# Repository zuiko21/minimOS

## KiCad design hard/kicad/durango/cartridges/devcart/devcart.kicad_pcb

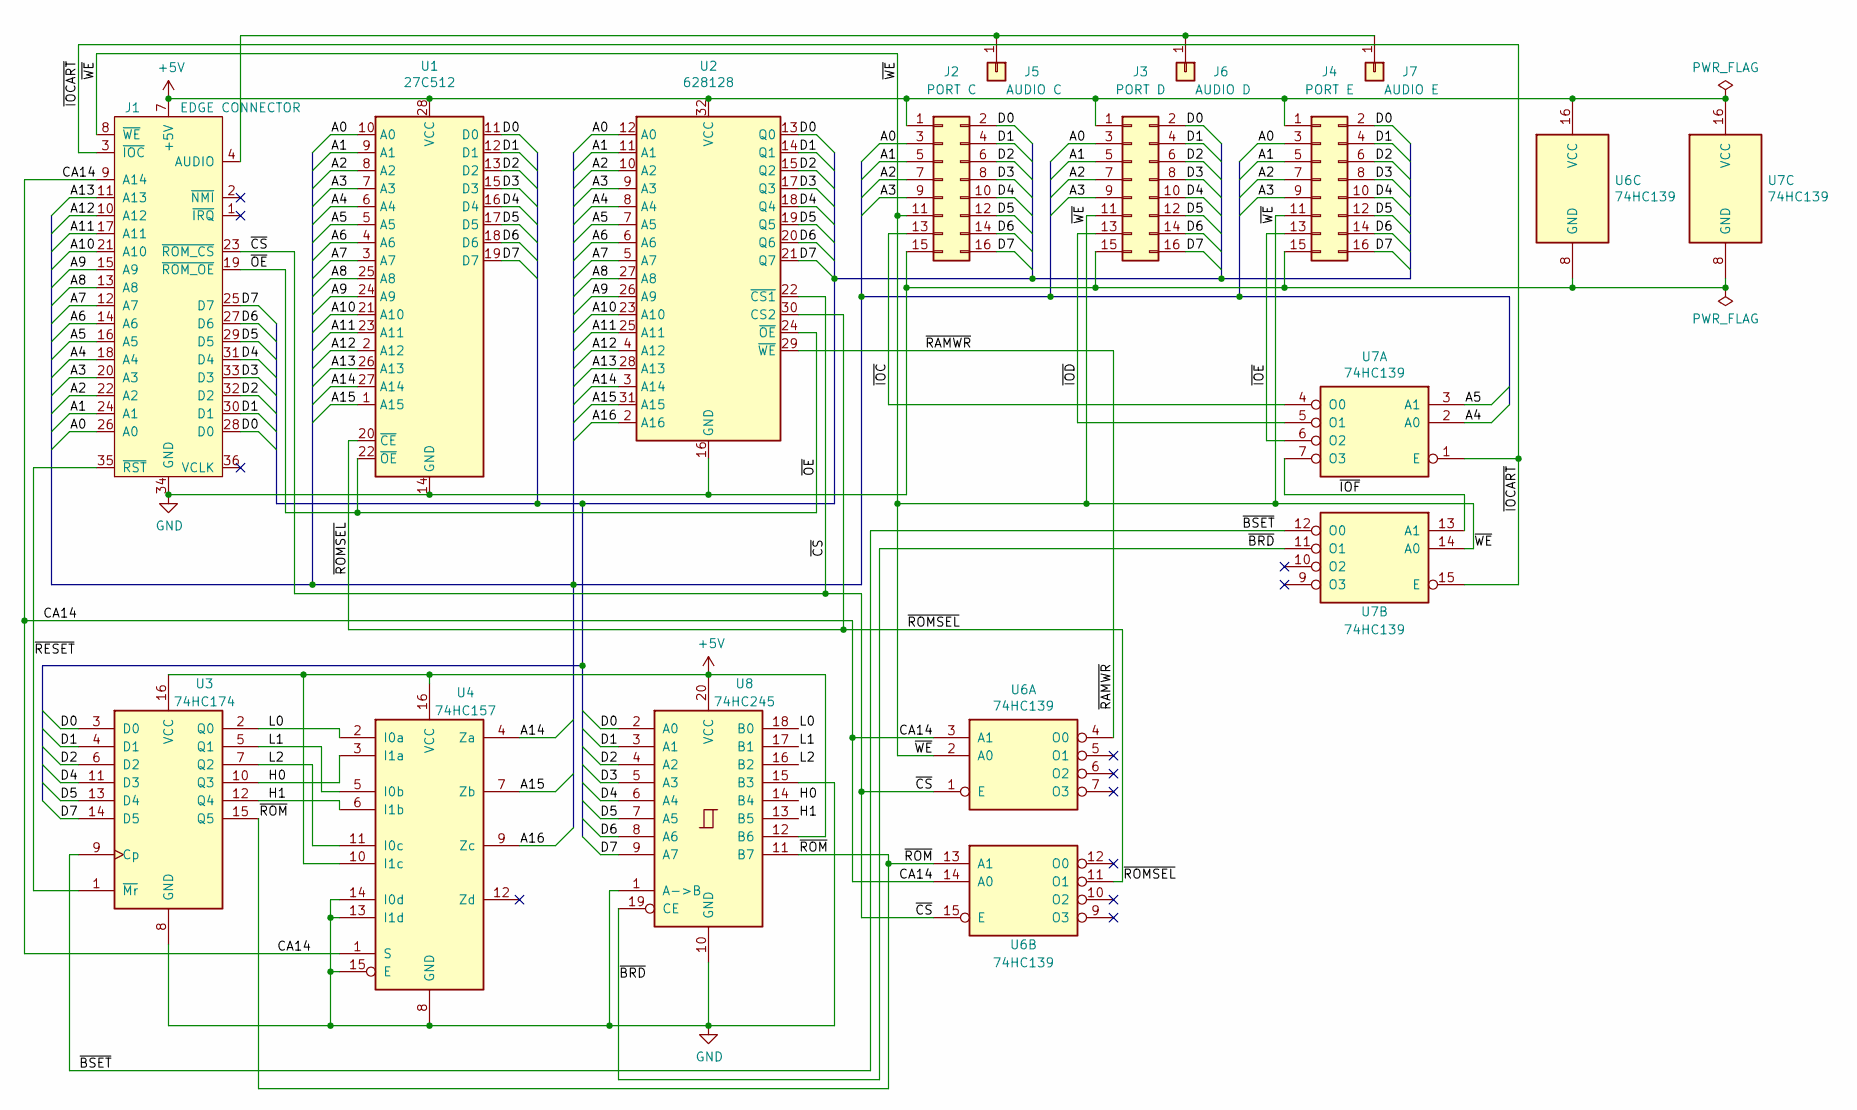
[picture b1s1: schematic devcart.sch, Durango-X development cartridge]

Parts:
J1: EDGE CONNECTOR; Durango_ROM
J2: PORT C; IDC-Header_2x08_P2.54mm_Vertical
J3: PORT D; IDC-Header_2x08_P2.54mm_Vertical
J4: PORT E; IDC-Header_2x08_P2.54mm_Vertical
J5: AUDIO C; PinSocket_1x01_P2.54mm_Vertical
J6: AUDIO D; PinSocket_1x01_P2.54mm_Vertical
J7: AUDIO E; PinSocket_1x01_P2.54mm_Vertical
U1: 27C512; DIP_Socket-28_W11.9_W12.7_W15.24_W17.78_W18.5_3M_228-1277-0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
U2: 628128; DIP-32_W15.24mm
U3: 74HC174; DIP-16_W7.62mm
U4: 74HC157; DIP-16_W7.62mm
U6, U7: 74HC139; DIP-16_W7.62mm
U8: 74HC245; DIP-20_W7.62mm

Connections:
+5V: J1.7 (+5V), J2.1, J3.1, J4.1, U1.28 (VCC), U2.32 (VCC), U3.16 (VCC), U4.10 (I1c), U4.16 (VCC), U6.16 (VCC), U7.16 (VCC), U8.12 (B6), U8.20 (VCC)
/A0: J1.26 (A0), J2.3, J3.3, J4.3, U1.10 (A0), U2.12 (A0)
/A1: J1.24 (A1), J2.5, J3.5, J4.5, U1.9 (A1), U2.11 (A1)
/A2: J1.22 (A2), J2.7, J3.7, J4.7, U1.8 (A2), U2.10 (A2)
/A3: J1.20 (A3), J2.9, J3.9, J4.9, U1.7 (A3), U2.9 (A3)
/A4: J1.18 (A4), U1.6 (A4), U2.8 (A4), U7.2 (A0)
/A5: J1.16 (A5), U1.5 (A5), U2.7 (A5), U7.3 (A1)
/A6: J1.14 (A6), U1.4 (A6), U2.6 (A6)
/A7: J1.12 (A7), U1.3 (A7), U2.5 (A7)
/A8: J1.13 (A8), U1.25 (A8), U2.27 (A8)
/A9: J1.15 (A9), U1.24 (A9), U2.26 (A9)
/A10: J1.21 (A10), U1.21 (A10), U2.23 (A10)
/A11: J1.17 (A11), U1.23 (A11), U2.25 (A11)
/A12: J1.10 (A12), U1.2 (A12), U2.4 (A12)
/A13: J1.11 (A13), U1.26 (A13), U2.28 (A13)
/A14: U1.27 (A14), U2.3 (A14), U4.4 (Za)
/A15: U1.1 (A15), U2.31 (A15), U4.7 (Zb)
/A16: U2.2 (A16), U4.9 (Zc)
/CA14: J1.9 (A14), U4.1 (S), U6.3 (A1), U6.14 (A0)
/D0: J1.28 (D0), J2.2, J3.2, J4.2, U1.11 (D0), U2.13 (Q0), U3.3 (D0), U8.2 (A0)
/D1: J1.30 (D1), J2.4, J3.4, J4.4, U1.12 (D1), U2.14 (Q1), U3.4 (D1), U8.3 (A1)
/D2: J1.32 (D2), J2.6, J3.6, J4.6, U1.13 (D2), U2.15 (Q2), U3.6 (D2), U8.4 (A2)
/D3: J1.33 (D3), J2.8, J3.8, J4.8, U1.15 (D3), U2.17 (Q3), U8.5 (A3)
/D4: J1.31 (D4), J2.10, J3.10, J4.10, U1.16 (D4), U2.18 (Q4), U3.11 (D3), U8.6 (A4)
/D5: J1.29 (D5), J2.12, J3.12, J4.12, U1.17 (D5), U2.19 (Q5), U3.13 (D4), U8.7 (A5)
/D6: J1.27 (D6), J2.14, J3.14, J4.14, U1.18 (D6), U2.20 (Q6), U8.8 (A6)
/D7: J1.25 (D7), J2.16, J3.16, J4.16, U1.19 (D7), U2.21 (Q7), U3.14 (D5), U8.9 (A7)
/H0: U3.10 (Q3), U4.3 (I1a), U8.14 (B4)
/H1: U3.12 (Q4), U4.6 (I1b), U8.13 (B5)
/L0: U3.2 (Q0), U4.2 (I0a), U8.18 (B0)
/L1: U3.5 (Q1), U4.5 (I0b), U8.17 (B1)
/L2: U3.7 (Q2), U4.11 (I0c), U8.16 (B2)
/~BRD: U7.11 (O1), U8.19 (CE)
/~BSET: U3.9 (Cp), U7.12 (O0)
/~CS: J1.23 (~ROM_CS), U2.22 (~CS1), U6.1 (E), U6.15 (E)
/~IOC: J2.13, U7.4 (O0)
/~IOCART: J1.3 (~IOC), U7.1 (E), U7.15 (E)
/~IOD: J3.13, U7.5 (O1)
/~IOE: J4.13, U7.6 (O2)
/~IOF: U7.7 (O3), U7.13 (A1)
/~OE: J1.19 (~ROM_OE), U1.22 (~OE), U2.24 (~OE)
/~RAMWR: U2.29 (~WE), U6.4 (O0)
/~RESET: J1.35 (~RST), U3.1 (~Mr)
/~ROM: U3.15 (Q5), U6.13 (A1), U8.11 (B7)
/~ROMSEL: U1.20 (~CE), U2.30 (CS2), U6.11 (O1)
/~WE: J1.8 (~WE), J2.11, J3.11, J4.11, U6.2 (A0), U7.14 (A0)
GND: J1.34 (GND), J2.15, J3.15, J4.15, U1.14 (GND), U2.16 (GND), U3.8 (GND), U4.8 (GND), U4.13 (I1d), U4.14 (I0d), U4.15 (E), U6.8 (GND), U7.8 (GND), U8.1 (A->B), U8.10 (GND), U8.15 (B3)
unnamed: J1.4 (AUDIO), J5.1, J6.1, J7.1

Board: 2 copper layers, 14 parts (0 on the bottom side), 48 nets, no tracks yet.

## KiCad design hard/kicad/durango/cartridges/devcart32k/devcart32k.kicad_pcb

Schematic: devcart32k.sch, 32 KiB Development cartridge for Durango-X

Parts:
C1: 22n; C_Rect_L7.0mm_W3.5mm_P5.00mm
J1: to Computer; Durango_ROM
J2: SD Interface; PinHeader_2x08_P2.54mm_Vertical
LOGO1: Logo_Open_Hardware_Large; OSHW-Logo2_24.3x20mm_SilkScreen
LOGO2: Logo_Open_Hardware_Small; jaqueria
LOGO3: Logo_Open_Hardware_Small; durango-x90
U1: 27/28C256; DIP_Socket-28_W11.9_W12.7_W15.24_W17.78_W18.5_3M_228-1277-0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
U2: 62256; DIP-28_W15.24mm_Socket
U4: 74HC174; DIP-16_W7.62mm_Socket
U5, U7: 74HC139; DIP-16_W7.62mm_Socket
U6: 74HC245; DIP-20_W7.62mm_Socket

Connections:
+5V: C1.2, J1.7, J2.5, J2.6, U1.1 (VPP), U1.27 (A14), U1.28 (VCC), U2.28 (VCC), U4.14 (D5), U4.16 (VCC), U5.16 (VCC), U6.14 (B4), U6.15 (B3), U6.20 (VCC), U7.14 (A0), U7.16 (VCC)
/G~WE: U2.27 (~WE~), U7.4 (O0)
/MCLK: J2.11, J2.12, U4.2 (Q0), U6.18 (B0)
/MISO: J2.13, J2.14, U6.11 (B7)
/MOSI: J2.9, J2.10, U4.5 (Q1), U6.17 (B1)
/RAM~OE: U2.22 (~OE~), U7.9 (O3)
/ROM~OE: U1.22 (~OE), U7.11 (O1)
/~BL0: U5.3 (A1), U5.12 (O0)
/~CS: J1.23, U1.20 (~CE), U2.20 (~CS), U7.1 (E)
/~IOC: J1.3, U5.1 (E)
/~LATCH: U4.9 (Cp), U5.4 (O0)
/~OE: J1.19, U7.15 (E)
/~ROMEN: U4.12 (Q4), U6.12 (B6), U7.13 (A1)
/~RST: J1.35, U4.1 (~Mr)
/~SSEL: J2.7, J2.8, U4.7 (Q2), U6.16 (B2)
/~STATUS: U5.5 (O1), U6.19 (CE)
/~WE: J1.8, U5.2 (A0), U7.2 (A0)
/~WRITEN: U4.10 (Q3), U6.13 (B5), U7.3 (A1)
A0: J1.26, U1.10 (A0), U2.10 (A0)
A1: J1.24, U1.9 (A1), U2.9 (A1)
A2: J1.22, U1.8 (A2), U2.8 (A2)
A3: J1.20, U1.7 (A3), U2.7 (A3), U5.15 (E)
A4: J1.18, U1.6 (A4), U2.6 (A4), U5.14 (A0)
A5: J1.16, U1.5 (A5), U2.5 (A5), U5.13 (A1)
A6: J1.14, U1.4 (A6), U2.4 (A6)
A7: J1.12, U1.3 (A7), U2.3 (A7)
A8: J1.13, U1.25 (A8), U2.25 (A8)
A9: J1.15, U1.24 (A9), U2.24 (A9)
A10: J1.21, U1.21 (A10), U2.21 (A10)
A11: J1.17, U1.23 (A11), U2.23 (A11)
A12: J1.10, U1.2 (A12), U2.2 (A12)
A13: J1.11, U1.26 (A13), U2.26 (A13)
A14: J1.9, U2.1 (A14)
D0: J1.28, U1.11 (D0), U2.11 (D0), U4.3 (D0), U6.2 (A0)
D1: J1.30, U1.12 (D1), U2.12 (D1), U4.4 (D1), U6.3 (A1)
D2: J1.32, U1.13 (D2), U2.13 (D2), U4.6 (D2), U6.4 (A2)
D3: J1.33, U1.15 (D3), U2.15 (D3), U6.5 (A3)
D4: J1.31, U1.16 (D4), U2.16 (D4), U6.6 (A4)
D5: J1.29, U1.17 (D5), U2.17 (D5), U4.11 (D3), U6.7 (A5)
D6: J1.27, U1.18 (D6), U2.18 (D6), U4.13 (D4), U6.8 (A6)
D7: J1.25, U1.19 (D7), U2.19 (D7), U6.9 (A7)
GND: C1.1, J1.34, J2.1, J2.2, J2.15, J2.16, U1.14 (GND), U2.14 (GND), U4.8 (GND), U5.8 (GND), U6.1 (A->B), U6.10 (GND), U7.8 (GND)

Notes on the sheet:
Upper 16K only
32 KiB RAM DevCart + SD $DFC0-$DFC7
D0 = MCLK D1 = MOSI D2 = ~SSEL D5 = ~WRITEN D6 = ~ROMEN D7 = MISO

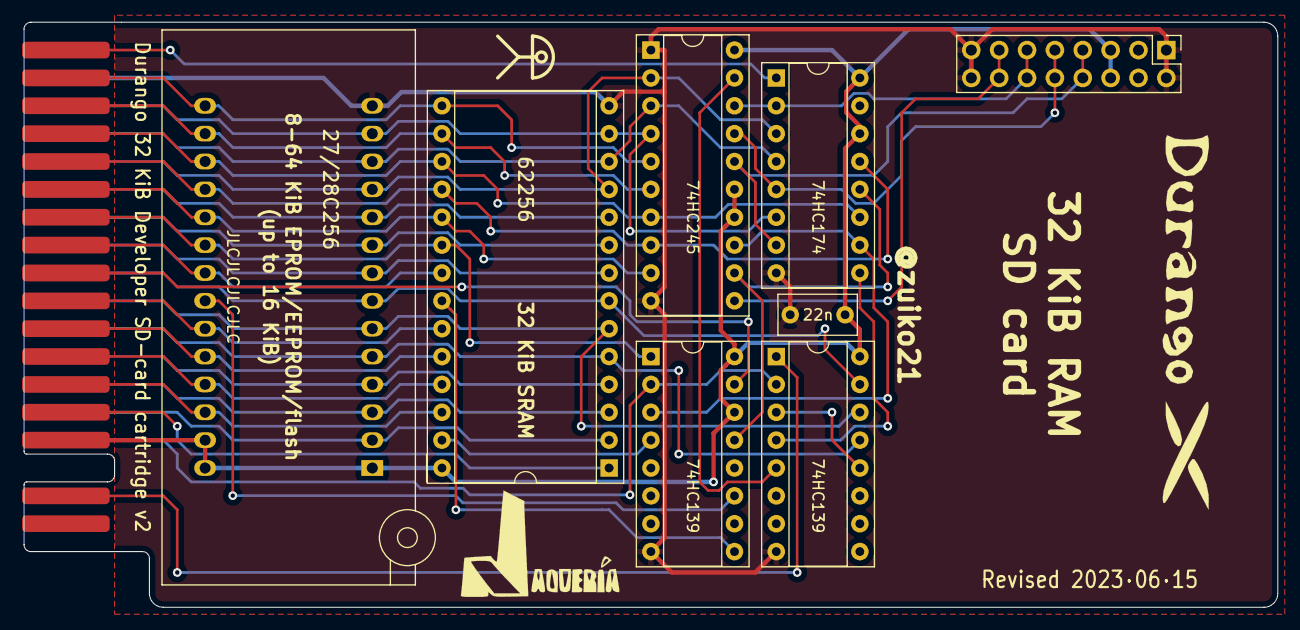
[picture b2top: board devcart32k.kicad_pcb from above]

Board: 2 copper layers, 114.3 x 53.3 mm, 12 parts (1 on the bottom side), 42 nets.

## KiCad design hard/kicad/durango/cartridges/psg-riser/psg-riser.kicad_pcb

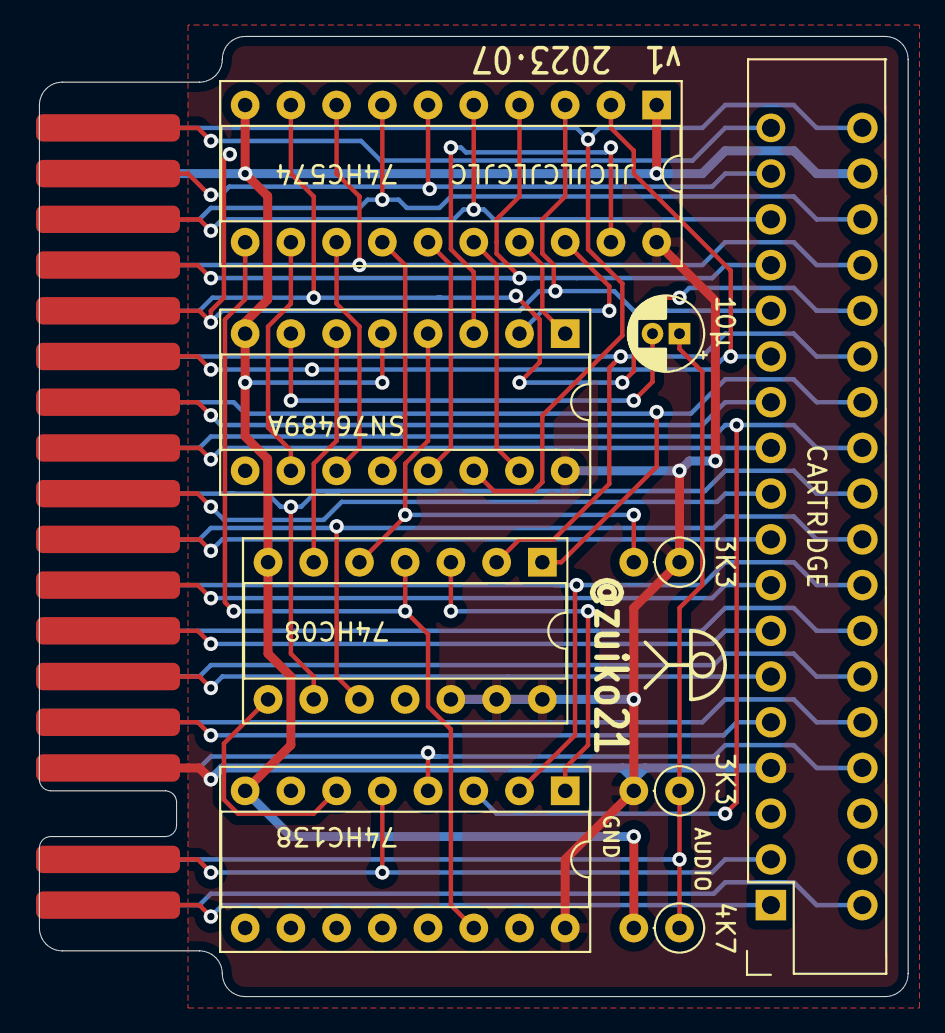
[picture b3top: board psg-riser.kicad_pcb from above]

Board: 2 copper layers, 48.3 x 53.3 mm, 11 parts (1 on the bottom side), 48 nets.

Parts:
C1: 10µ; CP_Radial_D4.0mm_P1.50mm
J1: Durango_ROM
J2: CARTRIDGE; PinSocket_2x18_EDGE
LOGO1: Logo_Open_Hardware_Small; j300
R1, R3: 3K3; R_Axial_DIN0207_L6.3mm_D2.5mm_P2.54mm_Vertical
R2: 4K7; R_Axial_DIN0207_L6.3mm_D2.5mm_P2.54mm_Vertical
U1: SN76489A; DIP-16_W7.62mm_Socket
U2: 74HC574; DIP-20_W7.62mm_Socket
U3: 74HC138; DIP-16_W7.62mm_Socket
U4: 74HC08; DIP-14_W7.62mm_Socket

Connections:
+5V: J1.7, J2.7, R1.2, R3.1, U1.16, U2.20, U3.16, U4.12, U4.13, U4.14
/A0: J1.26, J2.26, U4.2
/A0·1: U3.1, U4.3
/A1: J1.24, J2.24, U4.1
/A2: J1.22, J2.22, U3.3
/A3: J1.20, J2.20, U4.9
/A3·4: U3.6, U4.8
/A4: J1.18, J2.18, U4.10
/A5: J1.16, J2.16, U3.2
/A6: J1.14, J2.14
/A7: J1.12, J2.12
/A8: J1.13, J2.13
/A9: J1.15, J2.15
/A10: J1.21, J2.21
/A11: J1.17, J2.17
/A12: J1.10, J2.10
/A13: J1.11, J2.11
/A14: J1.9, J2.9
/AOUT: C1.2, U1.7
/AUDIO: C1.1, J1.4, R1.1, R2.1
/B0: U1.10, U2.12
/B1: U1.11, U2.13
/B2: U1.12, U2.14
/B3: U1.13, U2.15
/B4: U1.15, U2.16
/B5: U1.1, U2.17
/B6: U1.2, U2.18
/B7: U1.3, U2.19
/D0: J1.28, J2.28, U2.9
/D1: J1.30, J2.30, U2.8
/D2: J1.32, J2.32, U2.7
/D3: J1.33, J2.33, U2.6
/D4: J1.31, J2.31, U2.5
/D5: J1.29, J2.29, U2.4
/D6: J1.27, J2.27, U2.3
/D7: J1.25, J2.25, U2.2
/RDY: R3.2, U1.4, U4.5
/VCLK: J1.36, J2.36, U1.14
/~CS: J1.23, J2.23
/~IOC: J1.3, J2.3, U3.5
/~IRQ: J1.1, J2.1
/~NMI: J1.2, J2.2
/~OE: J1.19, J2.19
/~POE: U1.6, U4.6
/~PSG: U2.11, U3.14, U4.4
/~RST: J1.35, J2.35
/~WE: J1.8, J2.8, U3.4
GND: J1.34, J2.34, R2.2, U1.5, U1.8, U2.1, U2.10, U3.8, U4.7

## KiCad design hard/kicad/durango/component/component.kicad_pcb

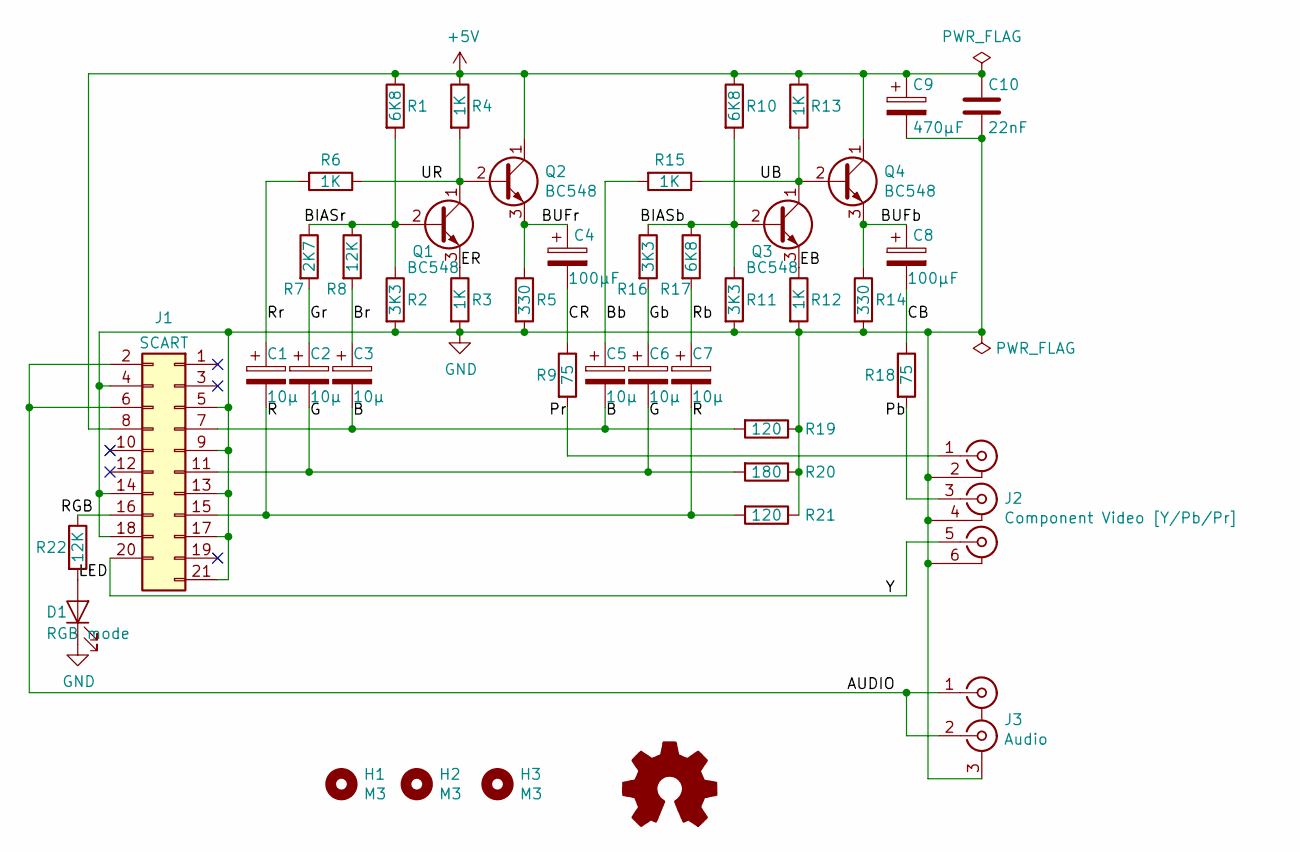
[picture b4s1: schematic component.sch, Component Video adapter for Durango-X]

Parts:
C1, C2, C3, C5, C6, C7: 10µ; CP_Radial_D4.0mm_P1.50mm
C4, C8: 100µF; CP_Radial_D4.0mm_P1.50mm
C9: 470µF; CP_Radial_D6.3mm_P2.50mm
C10: 22nF; C_Rect_L7.0mm_W2.0mm_P5.00mm
D1: RGB mode; LED_D3.0mm
H1, H2, H3: M3; MountingHole_3.2mm_M3_DIN965
J1: SCART
J2: Component Video [Y/Pb/Pr]; 3xRCA
J3: Audio; 2xRCA_vertical
LOGO1: Logo_Open_Hardware_Small; jaqueria
Q1, Q2, Q3, Q4: BC548; TO-92_Inline
R1, R10, R17: 6K8; R_Axial_DIN0207_L6.3mm_D2.5mm_P10.16mm_Horizontal
R2, R11, R16: 3K3; R_Axial_DIN0207_L6.3mm_D2.5mm_P10.16mm_Horizontal
R3, R4, R6, R12, R13, R15: 1K; R_Axial_DIN0207_L6.3mm_D2.5mm_P10.16mm_Horizontal
R5, R14: 330; R_Axial_DIN0207_L6.3mm_D2.5mm_P10.16mm_Horizontal
R7: 2K7; R_Axial_DIN0207_L6.3mm_D2.5mm_P10.16mm_Horizontal
R8, R22: 12K; R_Axial_DIN0207_L6.3mm_D2.5mm_P10.16mm_Horizontal
R9, R18: 75; R_Axial_DIN0207_L6.3mm_D2.5mm_P10.16mm_Horizontal
R19, R21: 120; R_Axial_DIN0207_L6.3mm_D2.5mm_P10.16mm_Horizontal
R20: 180; R_Axial_DIN0207_L6.3mm_D2.5mm_P10.16mm_Horizontal

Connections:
+5V: C9.1, C10.1, J1.8, Q2.1 (C), Q4.1 (C), R1.1, R4.1, R10.1, R13.1
/AUDIO: J1.2, J1.6, J3.1 (IN1), J3.2 (IN2)
/B: C3.2, C5.2, J1.7, R19.2
/BIASb: Q3.2 (B), R10.2, R11.1, R16.1, R17.1
/BIASr: Q1.2 (B), R1.2, R2.1, R7.1, R8.1
/BUFb: C8.1, Q4.3 (E), R14.1
/BUFr: C4.1, Q2.3 (E), R5.1
/Bb: C5.1, R15.2
/Br: C3.1, R8.2
/CB: C8.2, R18.1
/CR: C4.2, R9.1
/EB: Q3.3 (E), R12.1
/ER: Q1.3 (E), R3.1
/G: C2.2, C6.2, J1.11, R20.2
/Gb: C6.1, R16.2
/Gr: C2.1, R7.2
/LED: D1.2 (A), R22.2
/Pb: J2.3 (IN2), R18.2
/Pr: J2.1 (IN1), R9.2
/R: C1.2, C7.2, J1.15, R21.2
/RGB: J1.16, R22.1
/Rb: C7.1, R17.2
/Rr: C1.1, R6.2
/UB: Q3.1 (C), Q4.2 (B), R13.2, R15.1
/UR: Q1.1 (C), Q2.2 (B), R4.2, R6.1
/Y: J1.20, J2.5 (IN3)
GND: C9.2, C10.2, D1.1 (K), J1.4, J1.5, J1.9, J1.13, J1.14, J1.17, J1.18, J1.21, J2.2 (GND1), J2.4 (GND2), J2.6 (GND3), J3.3 (EXT), R2.2, R3.2, R5.2, R11.2, R12.2, R14.2, R19.1, R20.1, R21.1

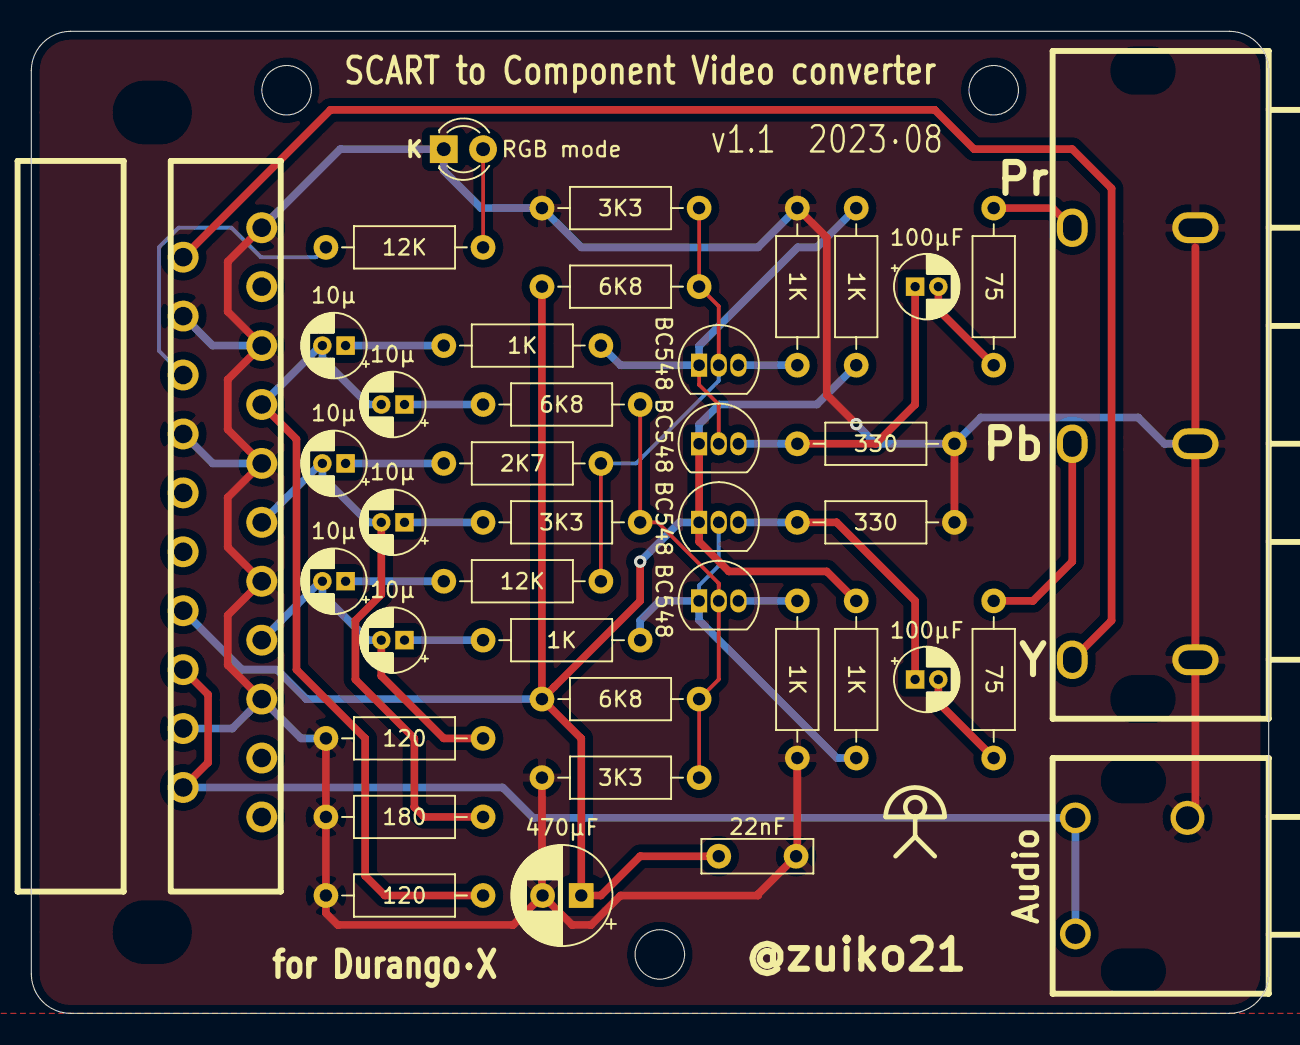
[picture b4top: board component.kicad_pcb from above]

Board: 2 copper layers, 80.0 x 63.5 mm, 44 parts (1 on the bottom side), 27 nets.

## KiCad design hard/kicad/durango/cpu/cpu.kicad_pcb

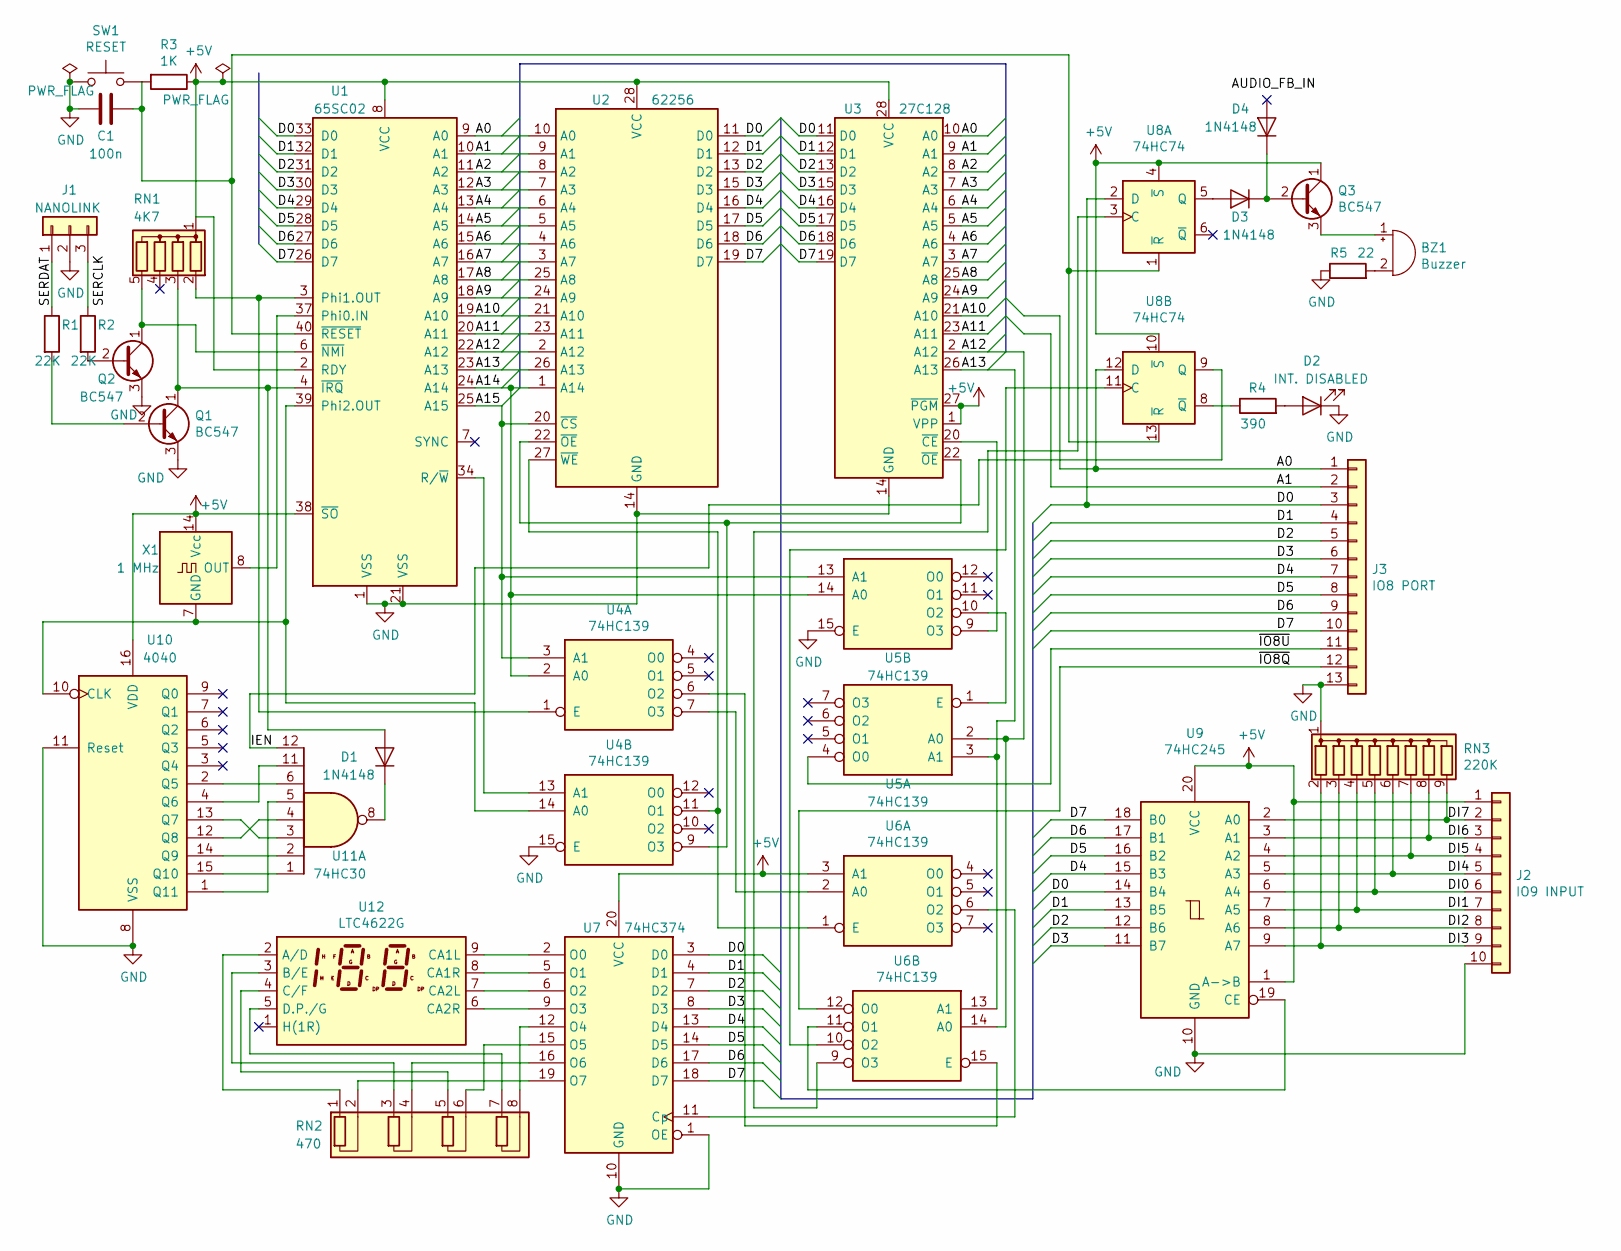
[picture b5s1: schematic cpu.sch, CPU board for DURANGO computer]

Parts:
BZ1: Buzzer; Buzzer_12x9.5RM7.6
C1: 100n; C_Rect_L10.0mm_W5.0mm_P5.00mm_P7.50mm
D1: 1N4148; D_DO-34_SOD68_P2.54mm_Vertical_AnodeUp
D2: INT. DISABLED; LED_D3.0mm
D3, D4: 1N4148; D_DO-35_SOD27_P7.62mm_Horizontal
J1: NANOLINK; PinHeader_1x03_P2.54mm_Vertical
J2: IO9 INPUT; PinHeader_1x10_P2.54mm_Vertical
J3: IO8 PORT; PinHeader_1x13_P2.54mm_Vertical
Q1, Q2, Q3: BC547; TO-92_Inline
R1, R2: 22K; R_Axial_DIN0204_L3.6mm_D1.6mm_P2.54mm_Vertical
R3: 1K; R_Axial_DIN0204_L3.6mm_D1.6mm_P2.54mm_Vertical
R4: 390; R_Axial_DIN0204_L3.6mm_D1.6mm_P2.54mm_Vertical
R5: 22; R_Axial_DIN0204_L3.6mm_D1.6mm_P2.54mm_Vertical
RN1: 4K7; R_Array_SIP5
RN2: 470; R_Array_SIP8
RN3: 220K; R_Array_SIP9
SW1: RESET; KSA_Tactile_SPST
U1: 65SC02; DIP-40_W15.24mm
U2: 62256; DIP-28_W15.24mm
U3: 27C128; DIP-28_W15.24mm
U4, U5, U6: 74HC139; DIP-16_W7.62mm
U7: 74HC374; DIP-20_W7.62mm
U8: 74HC74; DIP-14_W7.62mm
U9: 74HC245; DIP-20_W7.62mm
U10: 4040; DIP-16_W7.62mm
U11: 74HC30; DIP-14_W7.62mm
U12: LTC4622G; PinHeader_1x09_P2.54mm_Vertical
X1: 1 MHz; Oscillator_DIP-14

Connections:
+5V: J2.1, Q3.1 (C), R3.1, RN1.1 (common), U1.2 (RDY), U1.8 (VCC), U1.38 (~SO), U2.28 (VCC), U3.1 (VPP), U3.27 (~PGM), U3.28 (VCC), U4.16 (VCC), U5.16 (VCC), U6.3 (A1), U6.16 (VCC), U7.20 (VCC), U8.4 (~S), U8.10 (~S), U8.14 (VCC), U9.1 (A->B), U9.20 (VCC), U10.16 (VDD), U11.14 (VCC), X1.14 (Vcc)
/A0: J3.1, U1.9 (A0), U2.10 (A0), U3.10 (A0), U8.12 (D)
/A1: J3.2, U1.10 (A1), U2.9 (A1), U3.9 (A1)
/A2: U1.11 (A2), U2.8 (A2), U3.8 (A2)
/A3: U1.12 (A3), U2.7 (A3), U3.7 (A3)
/A4: U1.13 (A4), U2.6 (A4), U3.6 (A4)
/A5: U1.14 (A5), U2.5 (A5), U3.5 (A5)
/A6: U1.15 (A6), U2.4 (A6), U3.4 (A6)
/A7: U1.16 (A7), U2.3 (A7), U3.3 (A7)
/A8: U1.17 (A8), U2.25 (A8), U3.25 (A8)
/A9: U1.18 (A9), U2.24 (A9), U3.24 (A9)
/A10: U1.19 (A10), U2.21 (A10), U3.21 (A10)
/A11: U1.20 (A11), U2.23 (A11), U3.23 (A11)
/A12: U1.22 (A12), U2.2 (A12), U3.2 (A12), U5.2 (A0), U6.14 (A0)
/A13: U1.23 (A13), U2.26 (A13), U3.26 (A13), U5.3 (A1), U6.13 (A1)
/A14: U1.24 (A14), U2.1 (A14), U4.2 (A0), U5.14 (A0)
/A15: U1.25 (A15), U2.20 (~CS), U4.3 (A1), U5.13 (A1)
/D0: J3.3, U1.33 (D0), U2.11 (D0), U3.11 (D0), U7.3 (D0), U8.2 (D), U9.14 (B4)
/D1: J3.4, U1.32 (D1), U2.12 (D1), U3.12 (D1), U7.4 (D1), U9.13 (B5)
/D2: J3.5, U1.31 (D2), U2.13 (D2), U3.13 (D2), U7.7 (D2), U9.12 (B6)
/D3: J3.6, U1.30 (D3), U2.15 (D3), U3.15 (D3), U7.8 (D3), U9.11 (B7)
/D4: J3.7, U1.29 (D4), U2.16 (D4), U3.16 (D4), U7.13 (D4), U9.15 (B3)
/D5: J3.8, U1.28 (D5), U2.17 (D5), U3.17 (D5), U7.14 (D5), U9.16 (B2)
/D6: J3.9, U1.27 (D6), U2.18 (D6), U3.18 (D6), U7.17 (D6), U9.17 (B1)
/D7: J3.10, U1.26 (D7), U2.19 (D7), U3.19 (D7), U7.18 (D7), U9.18 (B0)
/DI0: J2.6, RN3.5 (R4), U9.6 (A4)
/DI1: J2.7, RN3.4 (R3), U9.7 (A5)
/DI2: J2.8, RN3.3 (R2), U9.8 (A6)
/DI3: J2.9, RN3.2 (R1), U9.9 (A7)
/DI4: J2.5, RN3.6 (R5), U9.5 (A3)
/DI5: J2.4, RN3.7 (R6), U9.4 (A2)
/DI6: J2.3, RN3.8 (R7), U9.3 (A1)
/DI7: J2.2, RN3.9 (R8), U9.2 (A0)
/IEN: U8.9 (Q), U11.12
/SERDAT: J1.1, R1.1
/~IO8Q: J3.12, U6.12 (O0)
/~IO8U: J3.11, U5.4 (O0)
unnamed: BZ1.1 (-), Q3.3 (E)
unnamed: BZ1.2 (+), R5.2
unnamed: C1.1, R3.2, SW1.2, U1.40 (~RESET), U8.1 (~R), U8.13 (~R)
unnamed: D1.1 (K), U11.8
unnamed: D1.2 (A), Q1.1 (C), RN1.3 (R2), U1.4 (~IRQ)
unnamed: D2.2 (A), R4.2
unnamed: D3.1 (K), D4.1 (K), Q3.2 (B)
unnamed: D3.2 (A), U8.5 (Q)
unnamed: J1.3, R2.1
unnamed: Q1.2 (B), R1.2
unnamed: Q2.1 (C), RN1.5 (R4), U1.6 (~NMI)
unnamed: Q2.2 (B), R2.2
unnamed: R4.1, U8.8 (~Q)
unnamed: RN1.2 (R1), U1.3 (Phi1.OUT), U4.1 (E)
unnamed: RN2.1 (R1.1), U12.2 (A/D)
unnamed: RN2.2 (R1.2), U7.19 (O7)
unnamed: RN2.3 (R2.1), U12.3 (B/E)
unnamed: RN2.4 (R2.2), U7.16 (O6)
unnamed: RN2.5 (R3.1), U12.4 (C/F)
unnamed: RN2.6 (R3.2), U7.15 (O5)
unnamed: RN2.7 (R4.1), U12.5 (D.P./G)
unnamed: RN2.8 (R4.2), U7.12 (O4)
unnamed: U1.34 (R/~W), U4.13 (A1)
unnamed: U1.37 (Phi0.IN), X1.8 (OUT)
unnamed: U2.22 (~OE~), U3.22 (~OE), U4.9 (O3)
unnamed: U2.27 (~WE~), U4.11 (O1), U6.1 (E)
unnamed: U3.20 (~CE), U5.9 (O3)
unnamed: U4.6 (O2), U6.15 (E)
unnamed: U4.7 (O3), U6.2 (A0)
unnamed: U5.1 (E), U5.10 (O2)
unnamed: U6.6 (O2), U7.11 (Cp)
unnamed: U6.9 (O3), U8.3 (C)
unnamed: U6.10 (O2), U8.11 (C)
unnamed: U6.11 (O1), U9.19 (CE)
unnamed: U10.1 (Q11), U11.5
unnamed: U10.2 (Q5), U11.6
unnamed: U10.4 (Q6), U11.11
unnamed: U10.12 (Q8), U11.4
unnamed: U10.13 (Q7), U11.3
unnamed: U10.14 (Q9), U11.2
unnamed: U10.15 (Q10), U11.1
unnamed: U7.9 (O3), U12.6 (CA2R)
unnamed: U7.6 (O2), U12.7 (CA2L)
unnamed: U7.5 (O1), U12.8 (CA1R)
unnamed: U7.2 (O0), U12.9 (CA1L)

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
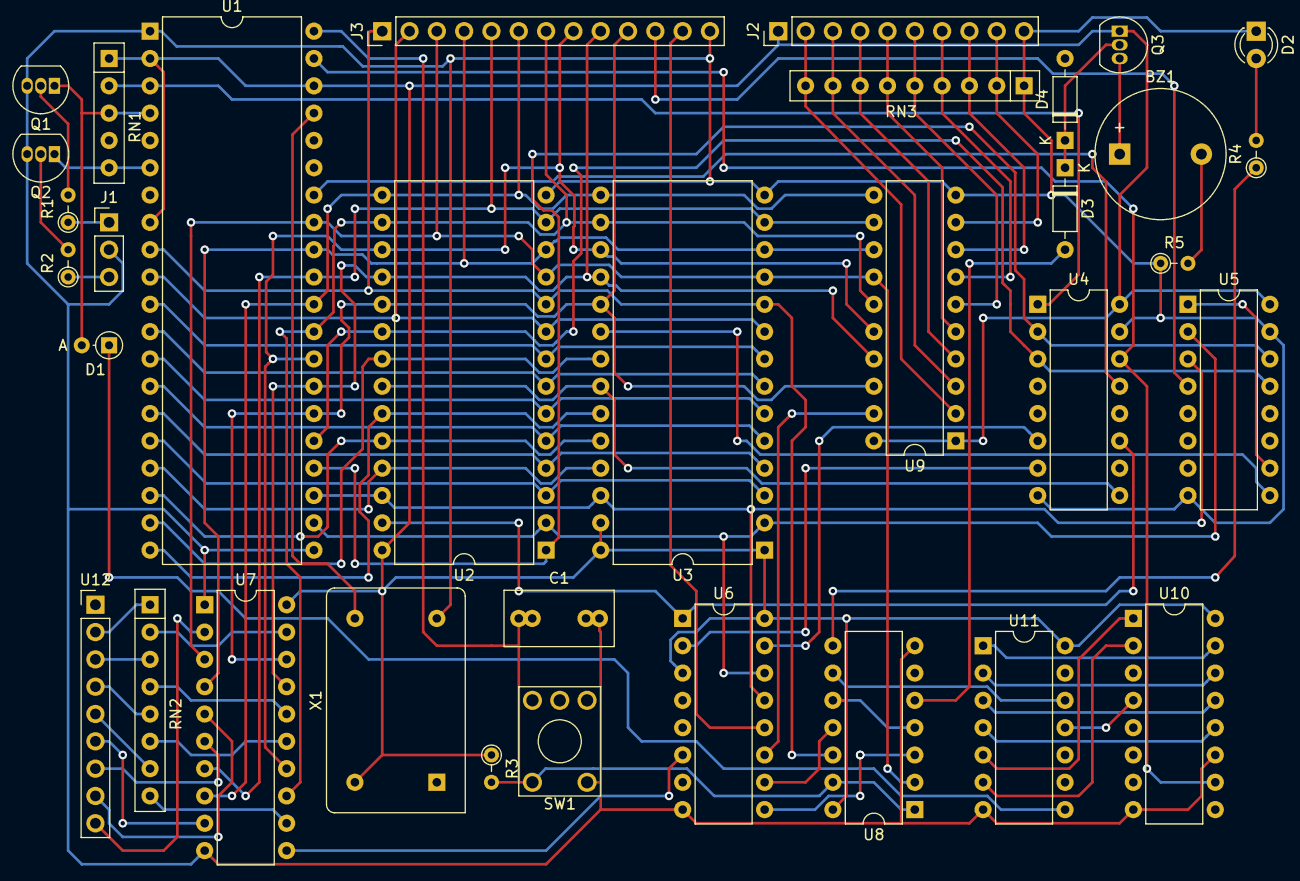
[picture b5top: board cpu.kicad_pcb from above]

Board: 2 copper layers, 34 parts (0 on the bottom side), 84 nets.

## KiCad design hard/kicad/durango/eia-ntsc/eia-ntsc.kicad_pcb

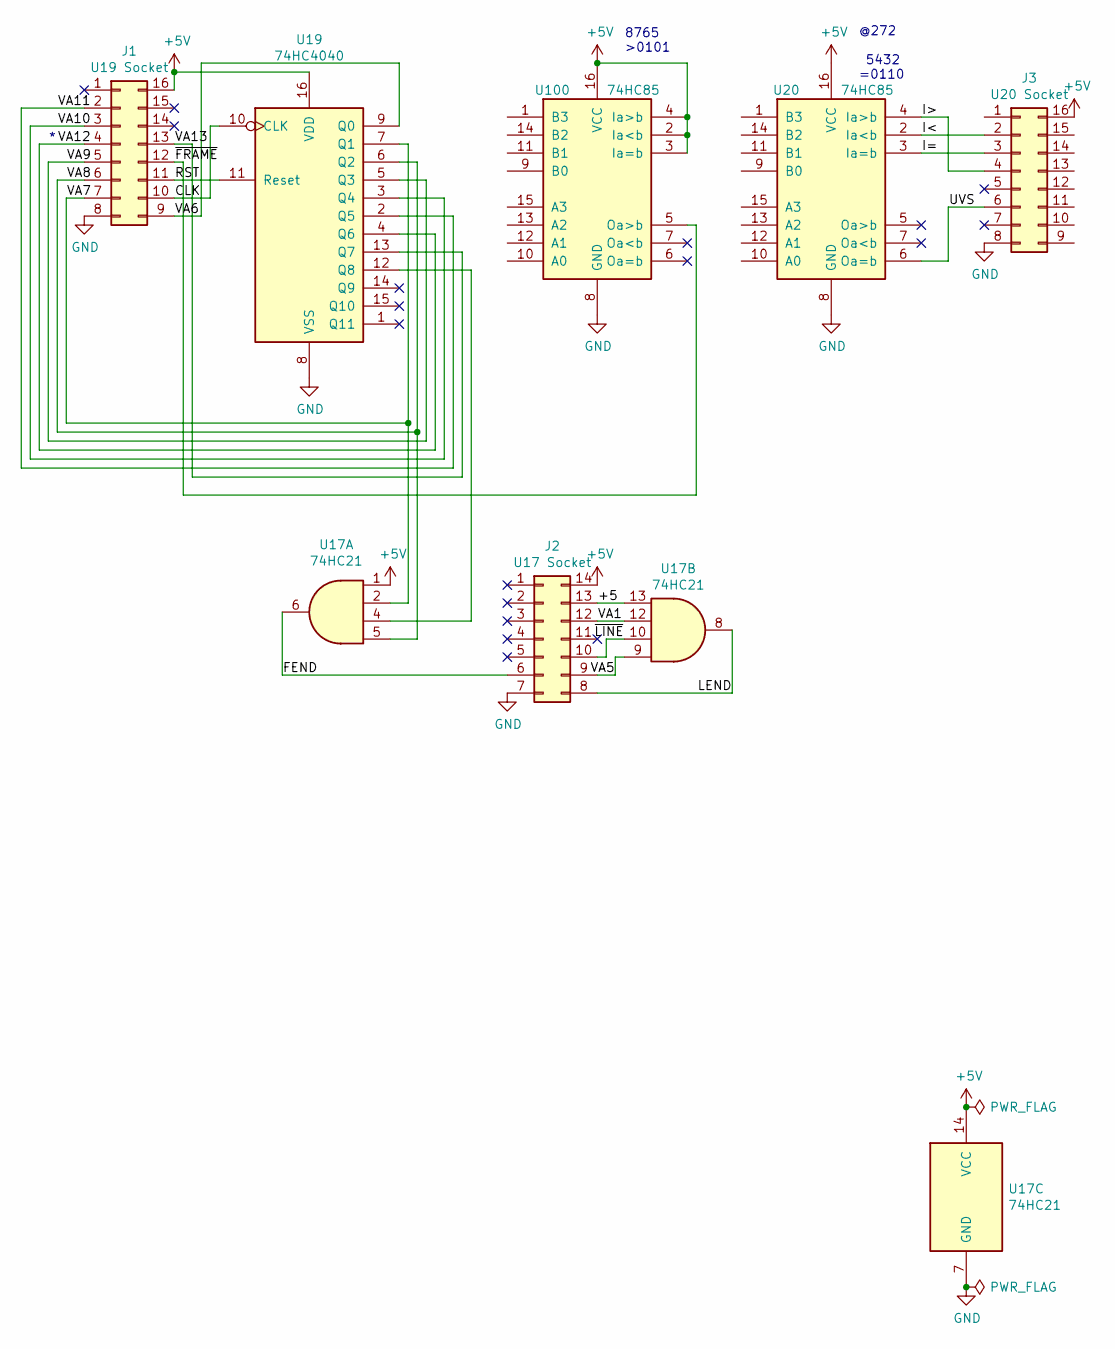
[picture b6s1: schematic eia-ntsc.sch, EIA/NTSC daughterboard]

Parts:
J1: U19 Socket; DIP-16_W7.62mm_Socket
J2: U17 Socket; DIP-14_W7.62mm_Socket
J3: U20 Socket; DIP-16_W7.62mm_Socket
U17: 74HC21; DIP-14_W7.62mm
U19: 74HC4040; DIP-16_W7.62mm
U20, U100: 74HC85; DIP-16_W7.62mm

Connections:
+5V: J1.16, J2.14, J3.16, U17.1, U17.14 (VCC), U19.16 (VDD), U20.16 (VCC), U100.2 (Ia<b), U100.3 (Ia=b), U100.4 (Ia>b), U100.16 (VCC)
/+5: J2.13, U17.13
/CLK: J1.10, U19.10 (CLK)
/FEND: J2.6, U17.6
/I<: J3.2, U20.2 (Ia<b)
/I=: J3.3, U20.3 (Ia=b)
/I>: J3.4, U20.4 (Ia>b)
/LEND: J2.8, U17.8
/RST: J1.11, U19.11 (Reset)
/UVS: J3.6, U20.6 (Oa=b)
/VA1: J2.12, U17.12
/VA5: J2.9, U17.9
/VA6: J1.9, U19.9 (Q0)
/VA7: J1.7, U17.2, U19.7 (Q1)
/VA8: J1.6, U17.5, U19.6 (Q2)
/VA9: J1.5, U19.5 (Q3)
/VA10: J1.3, U19.3 (Q4)
/VA11: J1.2, U19.2 (Q5)
/VA12: J1.4, U19.4 (Q6)
/VA13: J1.13, U19.13 (Q7)
/~FRAME: J1.12, U100.5 (Oa>b)
/~LINE: J2.10, U17.10
GND: J1.8, J2.7, J3.8, U17.7 (GND), U19.8 (VSS), U20.8 (GND), U100.8 (GND)
unnamed: U17.4, U19.12 (Q8)

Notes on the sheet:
@272 5432 =0110
8765 >0101

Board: 2 copper layers, 7 parts (0 on the bottom side), 24 nets, no tracks yet.

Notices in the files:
hard/kicad/durango/component/component.sch:
(c) 2023 Carlos J. Santisteban
hard/kicad/durango/cpu/cpu.sch:
(c) 2021 Carlos J. Santisteban
